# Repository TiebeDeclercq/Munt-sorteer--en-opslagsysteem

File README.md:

<!-- PROJECT LOGO -->
<br />
<div align="center">

  <h3 align="center">Coin sorting and storage system</h3>

  <p align="center">
    A coin-counting, storing, and dispensing system.
    <br />
    <a href="https://giptiebedeclercq.wordpress.com/"><strong>View the blog »</strong></a>
    <br />
    <br />
  </p>
</div>

<!-- ABOUT THE PROJECT -->
## About The Project

My design is a coin sorting and storage system aimed at effectively addressing the issue of loose change in the household. By storing all your coins in one central location, all the inconveniences of scattered small change are eliminated, and you have an accurate overview of your available loose change at all times. In this document, I will meticulously walk through the various phases of the project, detailing the development and implementation of the coin sorting and storage system step by step. All necessary information, including components and diagrams, is included in my document, accompanied by comprehensive explanations for a clear overview of the entire process.

## Download the software
This is the general software to control the coinsorting system for simply storing you're coins
<p float="left">
  <a href="https://play.google.com/store/apps/details?id=com.Ti3b3.Coin_sorting_and_storage_system"></img></a>
  <a href="https://l.messenger.com/l.php?u=http%3A%2F%2Fitunes.apple.com%2Fapp%2Fid6480136312&h=AT0W5dLV4-_HWo6Hpzhd1CNAs4ooRaiCPJcBq9KRZzaV246Ko3VcdnYeWSVa93cHaYDz-uc7uD9_STlt7n5DoX44x320C2RBlRl9Fa9wpZAEIEF3_ePi8t-rp98hANBxP2WmDY1l13mO-Vc"></img></a>
  <a href="https://apps.microsoft.com/detail/9ndc85wl55n7?hl=nl-nl&gl=BE"></img></a>
</p>

This is sofware/game to play flappy bird but you can play with multiple people and compete against eatchother 

<a href="https://ti3b3.itch.io/coin-sorting-and-storage-system-flappy-bird"></img></a>

<p align="right">(<a href="#readme-top">back to top</a>)</p>

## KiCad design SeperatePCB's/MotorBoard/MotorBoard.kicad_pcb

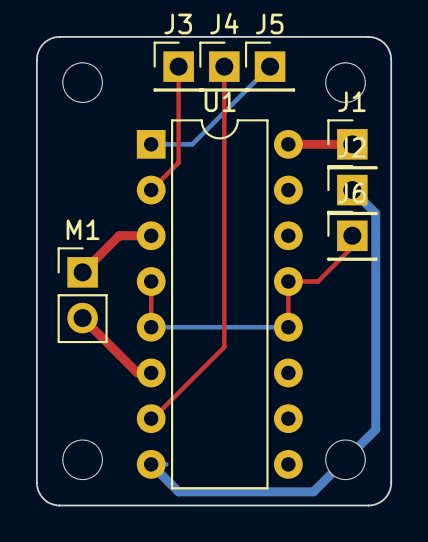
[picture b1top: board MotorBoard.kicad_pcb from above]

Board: 2 copper layers, 19.7 x 26.0 mm, 12 parts (0 on the bottom side), 8 nets.

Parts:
H1, H2, H3, H4: MountingHole; MountingHole_2.2mm_M2
J1, J2, J3, J4, J5, J6: Conn_01x01_Pin; PinHeader_1x01_P2.54mm_Vertical
M1: Motor_DC; PinHeader_1x02_P2.54mm_Vertical
U1: L293D; DIP-16_W7.62mm

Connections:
unnamed: J1.1, U1.16 (VCC1)
unnamed: J2.1, U1.8 (VCC2)
unnamed: J3.1, U1.2 (1A)
unnamed: J4.1, U1.7 (2A)
unnamed: J5.1, U1.1 (EN1,2)
unnamed: J6.1, U1.4 (GND), U1.5 (GND), U1.12 (GND), U1.13 (GND)
unnamed: M1.1 (+), U1.3 (1Y)
unnamed: M1.2 (-), U1.6 (2Y)

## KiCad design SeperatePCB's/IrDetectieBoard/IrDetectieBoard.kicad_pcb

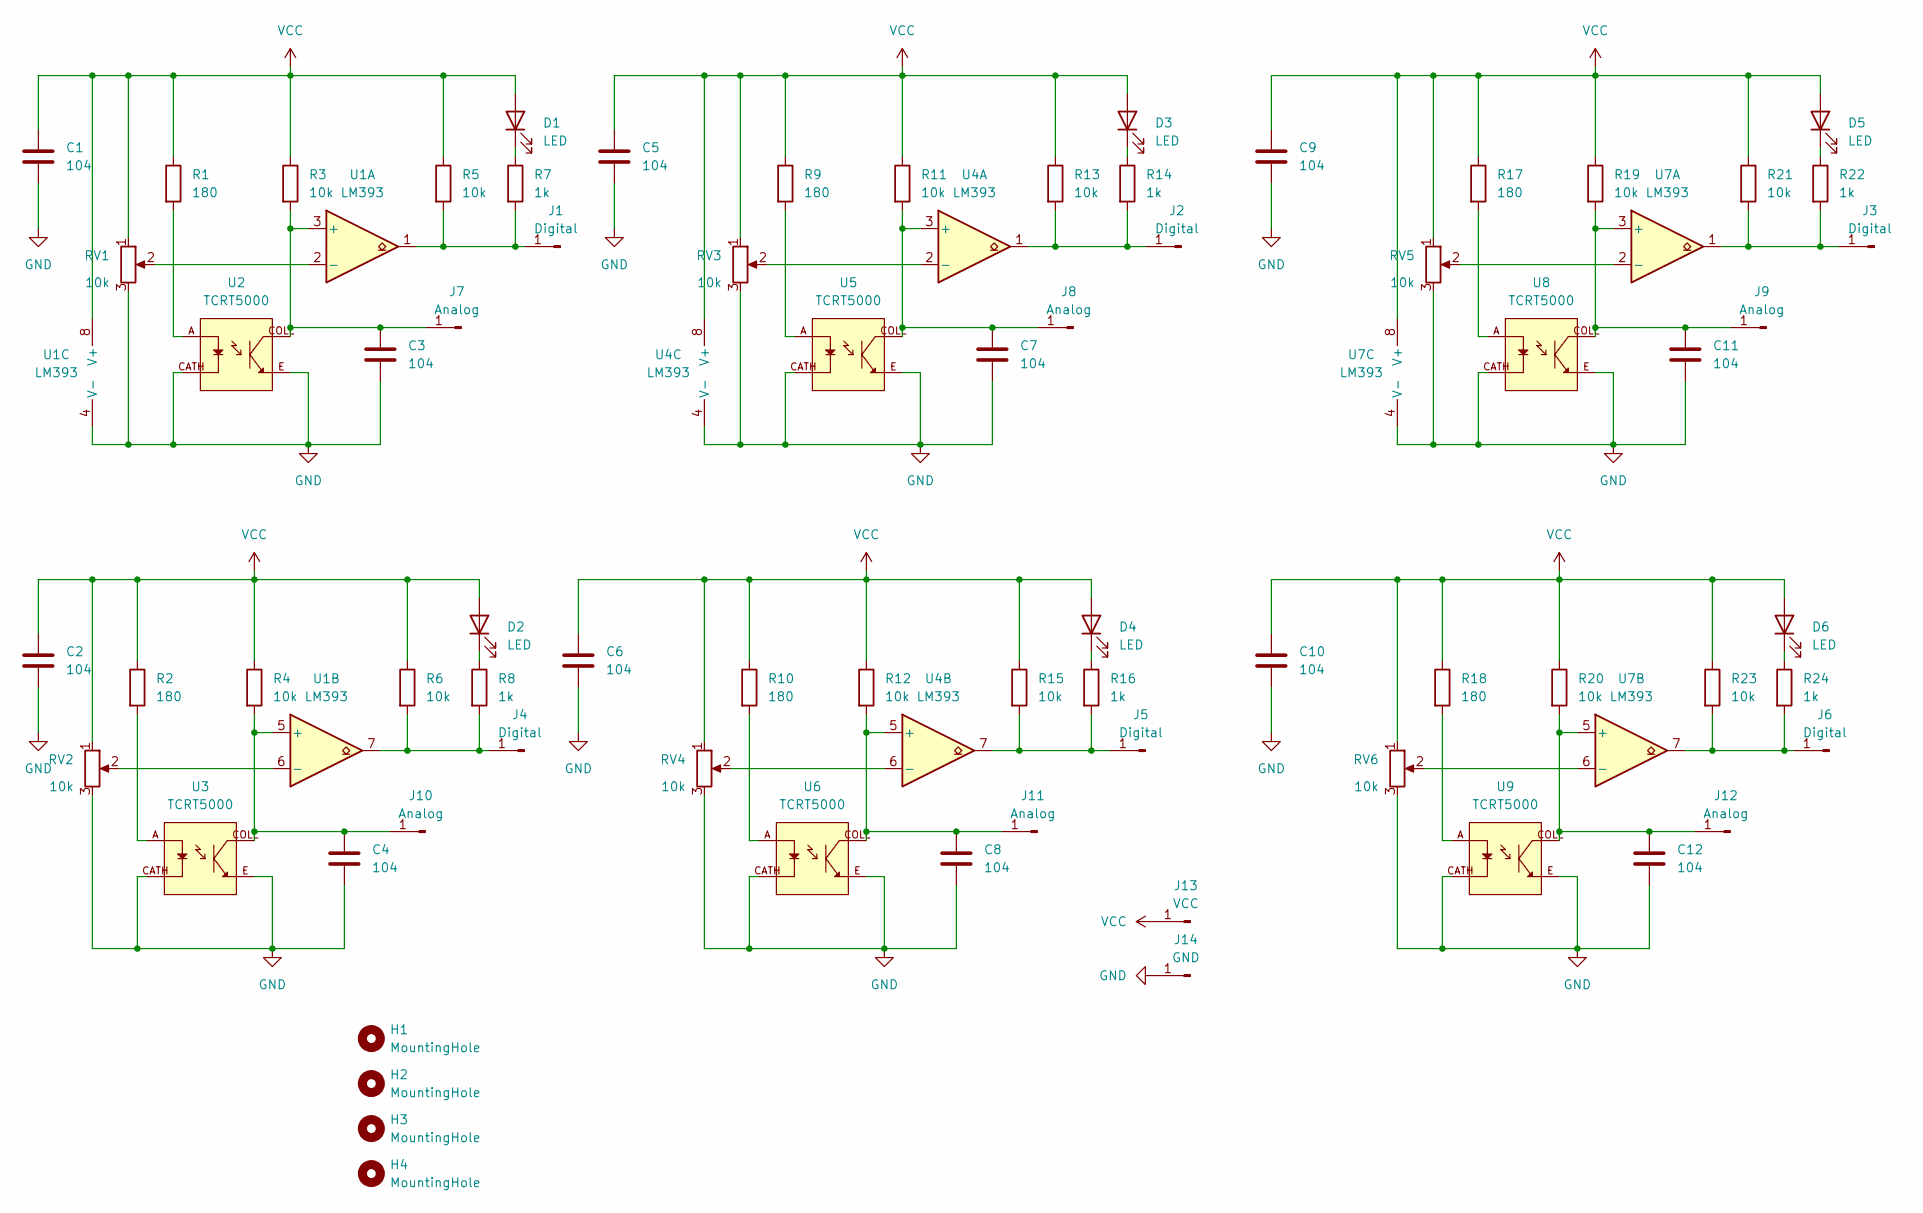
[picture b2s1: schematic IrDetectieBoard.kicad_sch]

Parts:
C1, C2, C3, C4, C5, C6, C7, C8, C9, C10, C11, C12: 104; C_0805_2012Metric_Pad1.18x1.45mm_HandSolder
D1, D2, D3, D4, D5, D6: LED; LED_0805_2012Metric_Pad1.15x1.40mm_HandSolder
H1, H2, H3, H4: MountingHole; MountingHole_2.2mm_M2
J1, J2, J3, J4, J5, J6: Digital; PinHeader_1x01_P2.54mm_Vertical
J7, J8, J9, J10, J11, J12: Analog; PinHeader_1x01_P2.54mm_Vertical
J13: VCC; PinHeader_1x01_P2.54mm_Vertical
J14: GND; PinHeader_1x01_P2.54mm_Vertical
R1, R2, R9, R10, R17, R18: 180; R_0805_2012Metric_Pad1.20x1.40mm_HandSolder
R3, R4, R5, R6, R11, R12, R13, R15, R19, R20, R21, R23: 10k; R_0805_2012Metric_Pad1.20x1.40mm_HandSolder
R7, R8, R14, R16, R22, R24: 1k; R_0805_2012Metric_Pad1.20x1.40mm_HandSolder
RV1, RV2, RV3, RV4, RV5, RV6: 10k; Potentiometer_Bourns_3296W_Vertical
U1, U4, U7: LM393; SO-8_3.9x4.9mm_P1.27mm
U2, U3, U5, U6, U8, U9: TCRT5000; PARTREV 1.7

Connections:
GND: C1.2, C2.2, C3.2, C4.2, C5.2, C6.2, C7.2, C8.2, C9.2, C10.2, C11.2, C12.2, J14.1, RV1.3, RV2.3, RV3.3, RV4.3, RV5.3, RV6.3, U1.4 (V-), U2.CATH, U2.E, U3.CATH, U3.E, U4.4 (V-), U5.CATH, U5.E, U6.CATH, U6.E, U7.4 (V-), U8.CATH, U8.E, U9.CATH, U9.E
unnamed: D1.1 (K), R7.1
unnamed: D2.1 (K), R8.1
unnamed: D3.1 (K), R14.1
unnamed: D4.1 (K), R16.1
unnamed: D5.1 (K), R22.1
unnamed: D6.1 (K), R24.1
unnamed: J1.1, R5.2, R7.2, U1.1
unnamed: J2.1, R13.2, R14.2, U4.1
unnamed: J3.1, R21.2, R22.2, U7.1
unnamed: J4.1, R6.2, R8.2, U1.7
unnamed: J5.1, R15.2, R16.2, U4.7
unnamed: J6.1, R23.2, R24.2, U7.7
unnamed: C3.1, J7.1, R3.2, U1.3 (+), U2.COLL
unnamed: C7.1, J8.1, R11.2, U4.3 (+), U5.COLL
unnamed: C11.1, J9.1, R19.2, U7.3 (+), U8.COLL
unnamed: C4.1, J10.1, R4.2, U1.5 (+), U3.COLL
unnamed: C8.1, J11.1, R12.2, U4.5 (+), U6.COLL
unnamed: C12.1, J12.1, R20.2, U7.5 (+), U9.COLL
unnamed: R1.2, U2.A
unnamed: R2.2, U3.A
unnamed: R9.2, U5.A
unnamed: R10.2, U6.A
unnamed: R17.2, U8.A
unnamed: R18.2, U9.A
unnamed: RV1.2, U1.2 (-)
unnamed: RV2.2, U1.6 (-)
unnamed: RV3.2, U4.2 (-)
unnamed: RV4.2, U4.6 (-)
unnamed: RV5.2, U7.2 (-)
unnamed: RV6.2, U7.6 (-)
VCC: C1.1, C2.1, C5.1, C6.1, C9.1, C10.1, D1.2 (A), D2.2 (A), D3.2 (A), D4.2 (A), D5.2 (A), D6.2 (A), J13.1, R1.1, R2.1, R3.1, R4.1, R5.1, R6.1, R9.1, R10.1, R11.1, R12.1, R13.1, R15.1, R17.1, R18.1, R19.1, R20.1, R21.1, R23.1, RV1.1, RV2.1, RV3.1, RV4.1, RV5.1, RV6.1, U1.8 (V+), U4.8 (V+), U7.8 (V+)

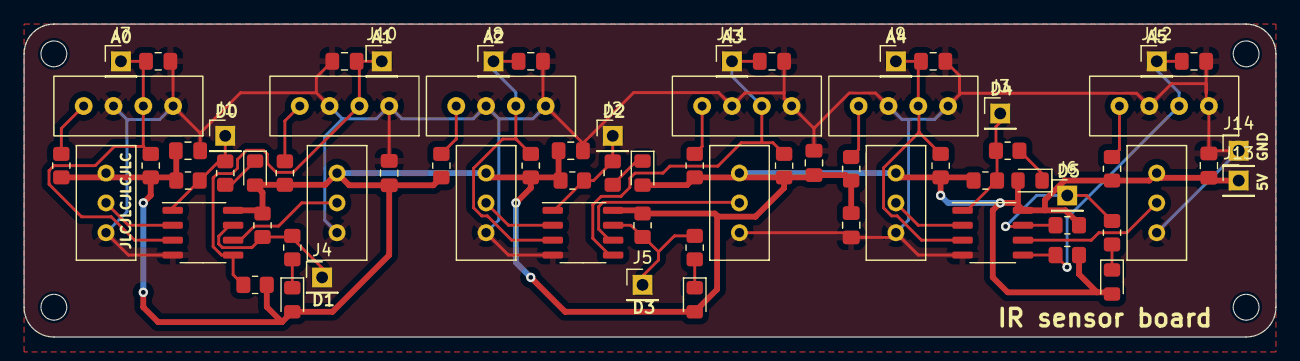
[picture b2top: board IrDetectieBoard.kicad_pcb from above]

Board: 2 copper layers, 106.7 x 26.7 mm, 75 parts (0 on the bottom side), 32 nets.

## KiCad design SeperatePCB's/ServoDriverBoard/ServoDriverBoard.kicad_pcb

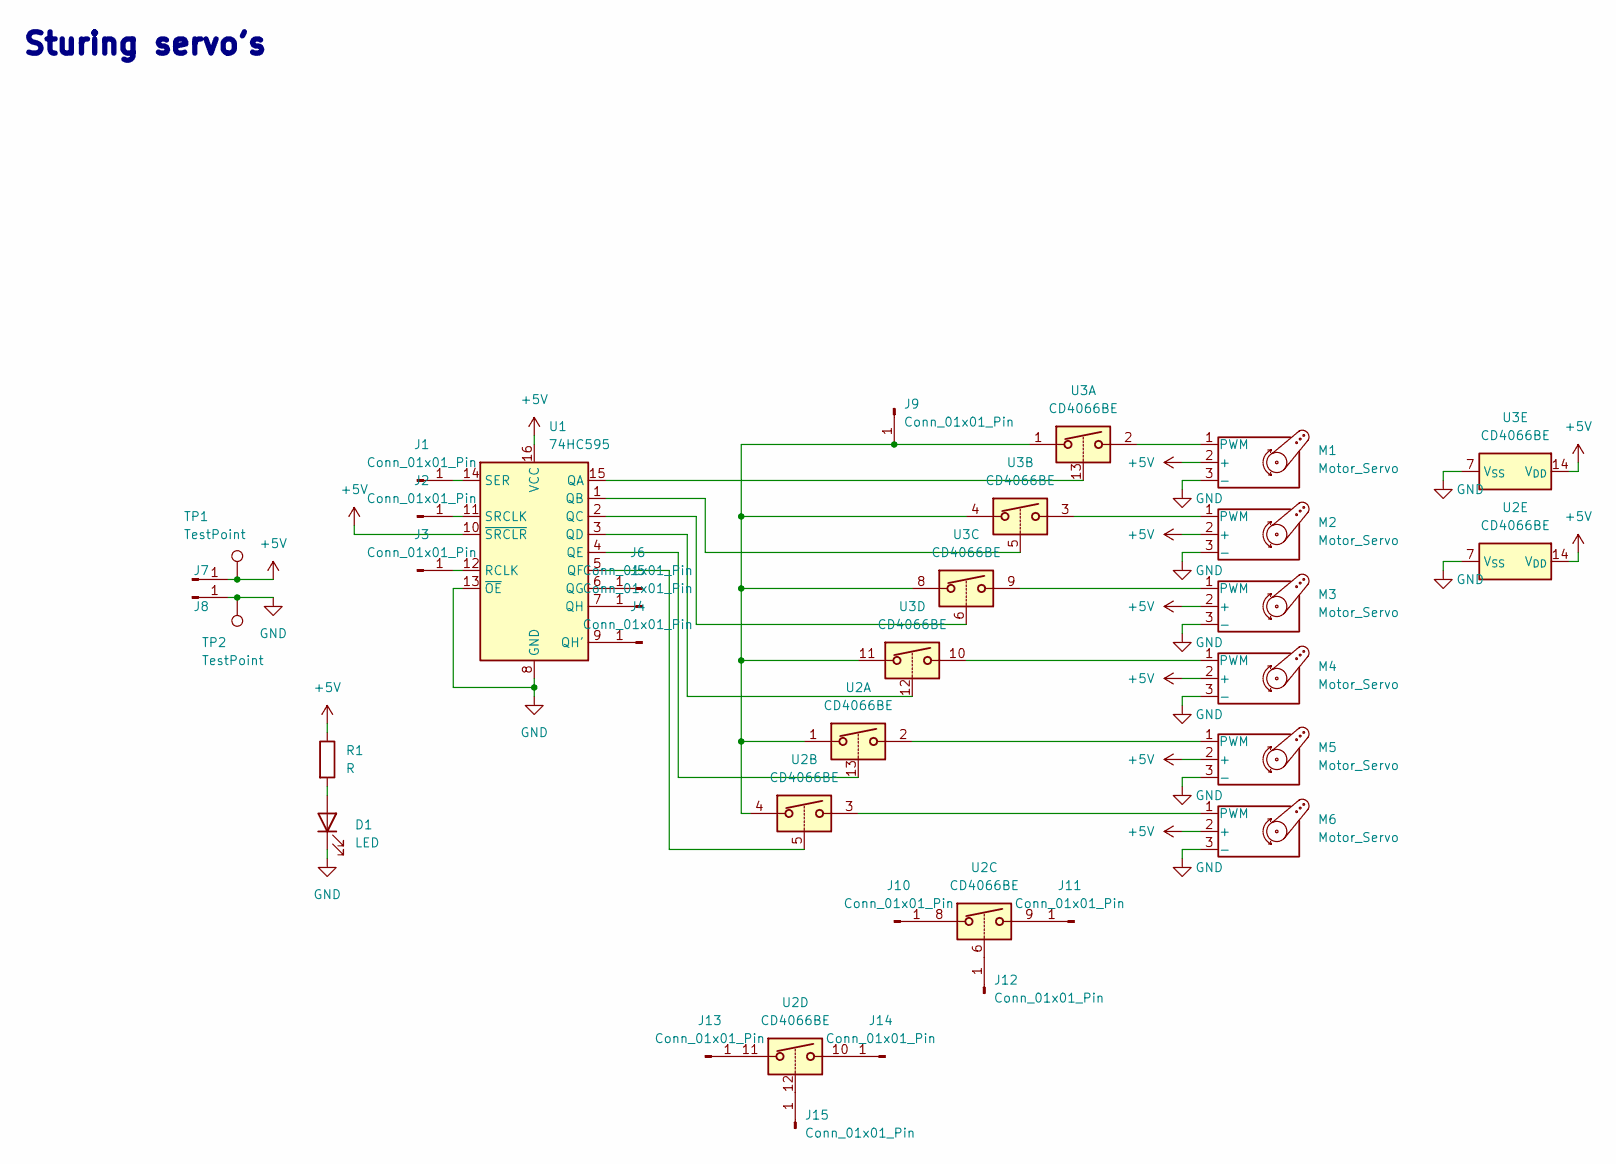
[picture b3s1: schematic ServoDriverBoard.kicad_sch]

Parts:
D1: LED; LED_0805_2012Metric_Pad1.15x1.40mm_HandSolder
J1, J2, J3, J4, J5, J6, J7, J8, J9, J10, J11, J12, J13, J14, J15: Conn_01x01_Pin; PinHeader_1x01_P2.54mm_Vertical
M1, M2, M3, M4, M5, M6: Motor_Servo; PinHeader_1x03_P2.54mm_Vertical
R1: R; R_0805_2012Metric_Pad1.20x1.40mm_HandSolder
TP1, TP2: TestPoint; TestPoint_Pad_D1.5mm
U1: 74HC595; DIP-16_W7.62mm_Socket
U2, U3: CD4066BE; DIP-14_W7.62mm_Socket

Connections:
+5V: J7.1, M1.2 (+), M2.2 (+), M3.2 (+), M4.2 (+), M5.2 (+), M6.2 (+), R1.1, TP1.1, U1.10 (~SRCLR), U1.16 (VCC), U2.14 (V_{DD}), U3.14 (V_{DD})
GND: D1.1 (K), J8.1, M1.3 (-), M2.3 (-), M3.3 (-), M4.3 (-), M5.3 (-), M6.3 (-), TP2.1, U1.8 (GND), U1.13 (~OE), U2.7 (V_{SS}), U3.7 (V_{SS})
unnamed: D1.2 (A), R1.2
unnamed: J1.1, U1.14 (SER)
unnamed: J2.1, U1.11 (SRCLK)
unnamed: J3.1, U1.12 (RCLK)
unnamed: J4.1, U1.9 (QH')
unnamed: J5.1, U1.7 (QH)
unnamed: J6.1, U1.6 (QG)
unnamed: J9.1, U2.1, U2.4, U3.1, U3.4, U3.8, U3.11
unnamed: J10.1, U2.8
unnamed: J11.1, U2.9
unnamed: J12.1, U2.6
unnamed: J13.1, U2.11
unnamed: J14.1, U2.10
unnamed: J15.1, U2.12
unnamed: M1.1 (PWM), U3.2
unnamed: M2.1 (PWM), U3.3
unnamed: M3.1 (PWM), U3.9
unnamed: M4.1 (PWM), U3.10
unnamed: M5.1 (PWM), U2.2
unnamed: M6.1 (PWM), U2.3
unnamed: U1.15 (QA), U3.13
unnamed: U1.1 (QB), U3.5
unnamed: U1.2 (QC), U3.6
unnamed: U1.3 (QD), U3.12
unnamed: U1.4 (QE), U2.13
unnamed: U1.5 (QF), U2.5

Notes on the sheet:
Sturing servo's

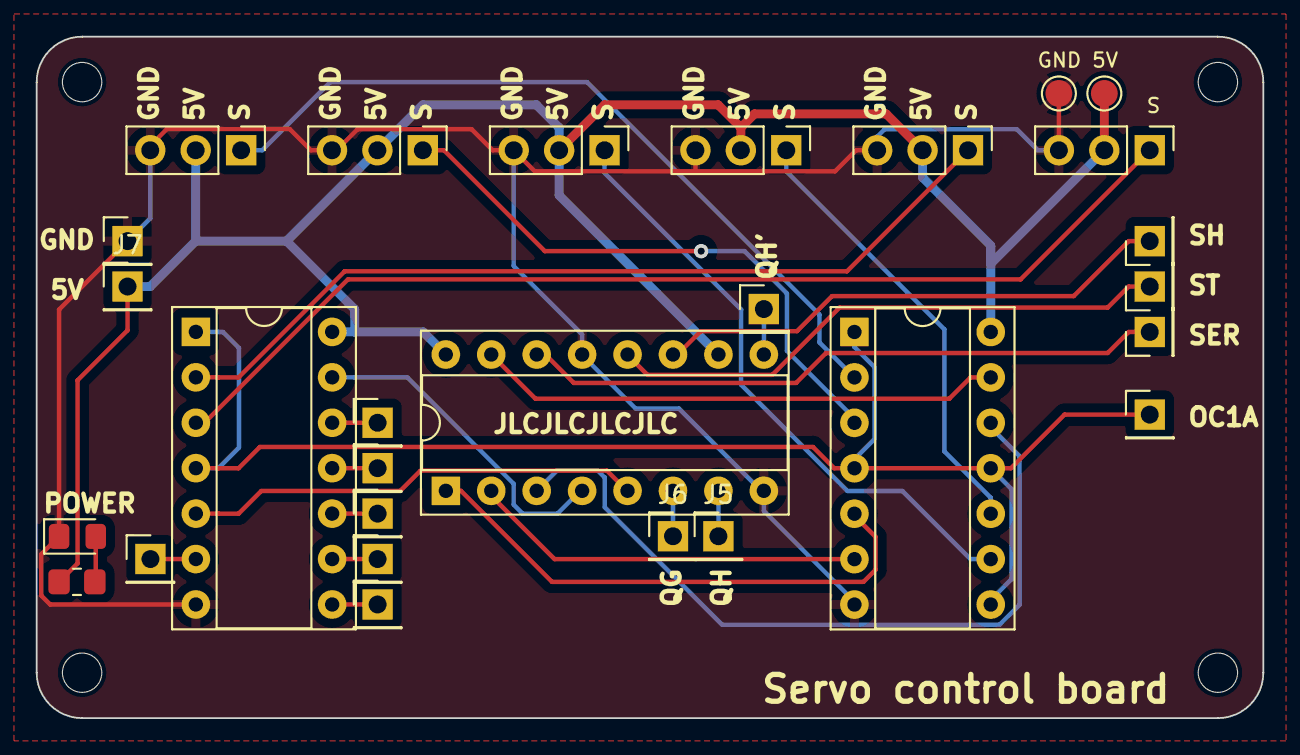
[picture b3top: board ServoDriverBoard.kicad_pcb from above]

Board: 2 copper layers, 68.6 x 38.1 mm, 32 parts (0 on the bottom side), 28 nets.

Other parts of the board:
H1, H2, H3, H4: MountingHole; MountingHole_2.2mm_M2

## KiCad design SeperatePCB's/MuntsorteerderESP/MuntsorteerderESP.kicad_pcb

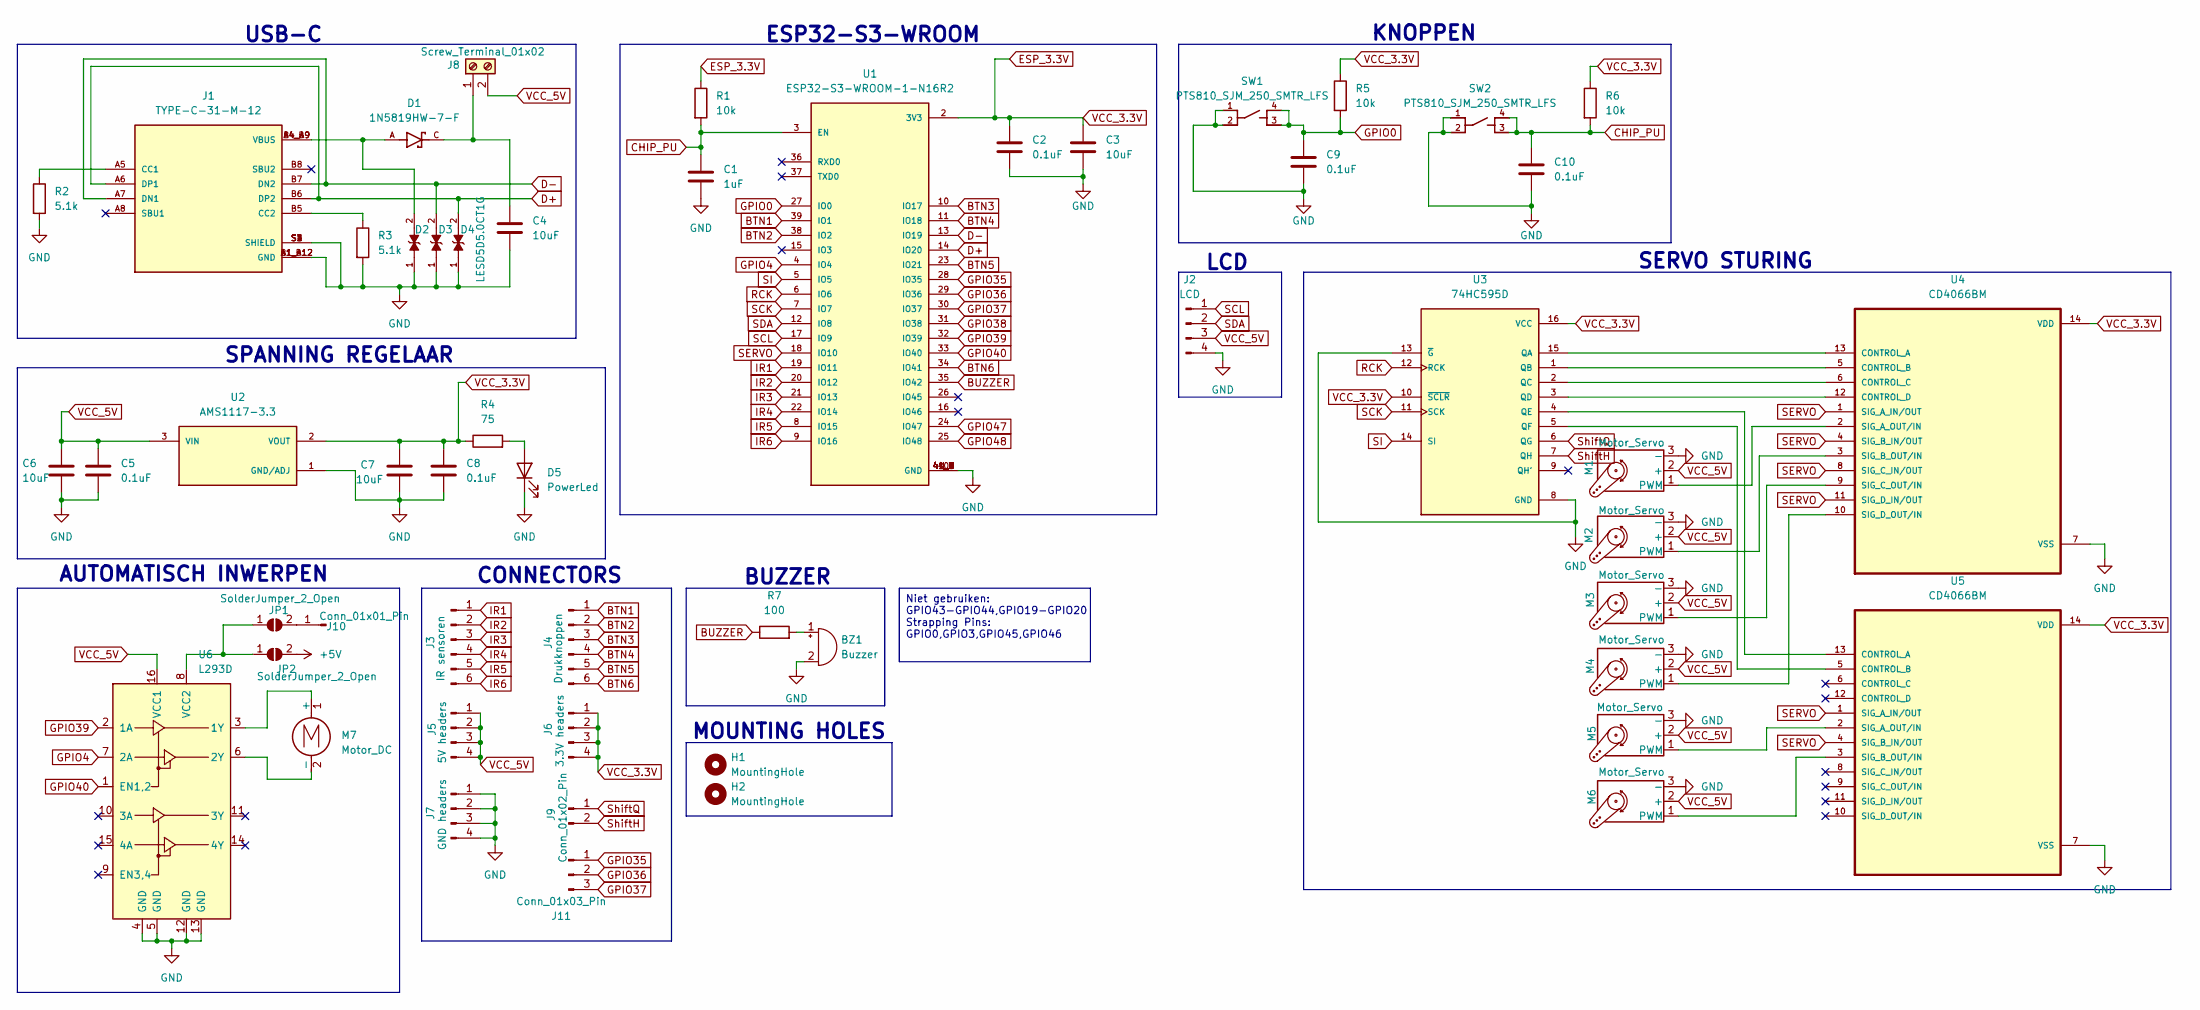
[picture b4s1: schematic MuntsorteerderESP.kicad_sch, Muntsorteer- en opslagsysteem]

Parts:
BZ1: Buzzer; Buzzer_12x9.5RM7.6
C1: 1uF; C_0805_2012Metric_Pad1.18x1.45mm_HandSolder
C2, C5, C8, C9, C10: 0.1uF; C_0805_2012Metric_Pad1.18x1.45mm_HandSolder
C3, C4, C6, C7: 10uF; C_0805_2012Metric_Pad1.18x1.45mm_HandSolder
D1: 1N5819HW-7-F; SOD3715X145N; PARTREV 18-2
D2, D3, D4: LESD5D5.0CT1G; TVS_LESD5D5.0CT1G; PARTREV O
D5: PowerLed; LED_0805_2012Metric
H1, H2: MountingHole; MountingHole_3.2mm_M3
J1: TYPE-C-31-M-12; HRO_TYPE-C-31-M-12; PARTREV 2020.12.08
J2: LCD; PinHeader_1x04_P2.54mm_Vertical
J3: IR sensoren; PinHeader_1x06_P2.54mm_Vertical
J4: Drukknoppen; PinHeader_1x06_P2.54mm_Vertical
J5: 5V headers; PinHeader_1x04_P2.54mm_Vertical
J6: 3.3V headers; PinHeader_1x04_P2.54mm_Vertical
J7: GND headers; PinHeader_1x04_P2.54mm_Vertical
J8: Screw_Terminal_01x02; TerminalBlock_Phoenix_MKDS-1,5-2-5.08_1x02_P5.08mm_Horizont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
J9: Conn_01x02_Pin; PinHeader_1x02_P2.54mm_Vertical
J10: Conn_01x01_Pin; PinHeader_1x01_P2.54mm_Vertical
J11: Conn_01x03_Pin; PinHeader_1x03_P2.54mm_Vertical
JP1, JP2: SolderJumper_2_Open; SolderJumper-2_P1.3mm_Open_RoundedPad1.0x1.5mm
M1, M2, M3, M4, M5, M6: Motor_Servo; PinHeader_1x03_P2.54mm_Vertical
M7: Motor_DC; TerminalBlock_Phoenix_MKDS-1,5-2-5.08_1x02_P5.08mm_Horizont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
R1, R5, R6: 10k; R_0805_2012Metric_Pad1.20x1.40mm_HandSolder
R2, R3: 5.1k; R_0805_2012Metric_Pad1.20x1.40mm_HandSolder
R4: 75; R_0805_2012Metric_Pad1.20x1.40mm_HandSolder
R7: 100; R_0805_2012Metric_Pad1.20x1.40mm_HandSolder
SW1, SW2: PTS810_SJM_250_SMTR_LFS; SW_PTS810_SJM_250_SMTR_LFS
U1: ESP32-S3-WROOM-1-N16R2; XCVR_ESP32-S3-WROOM-1-N16R2; PARTREV v1.0
U2: AMS1117-3.3; SOT229P700X180-4N; PARTREV N/A
U3: 74HC595D; SOP127P600X175-16N; PARTREV 4.0
U4, U5: CD4066BM; SOIC127P600X175-14N
U6: L293D; DIP-16_W7.62mm

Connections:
+5V: JP2.2 (B)
BTN1: J4.1, U1.39 (IO1)
BTN2: J4.2, U1.38 (IO2)
BTN3: J4.3, U1.10 (IO17)
BTN4: J4.4, U1.11 (IO18)
BTN5: J4.5, U1.23 (IO21)
BTN6: J4.6, U1.34 (IO41)
BUZZER: R7.1, U1.35 (IO42)
CHIP_PU: C1.1, C10.1, R1.2, R6.2, SW2.3, SW2.4, U1.3 (EN)
D+: D4.2, J1.A6 (DP1), J1.B6 (DP2), U1.14 (IO20)
D-: D3.2, J1.A7 (DN1), J1.B7 (DN2), U1.13 (IO19)
ESP_3.3V: C2.1, C3.1, C7.1, C8.1, J6.1, J6.2, J6.3, J6.4, R1.1, R4.1, R5.1, R6.1, U1.2 (3V3), U2.2 (VOUT), U3.10 (~SCLR), U3.16 (VCC), U4.14 (VDD), U5.14 (VDD)
GND: BZ1.2 (+), C1.2, C2.2, C3.2, C4.2, C5.2, C6.2, C7.2, C8.2, C9.2, C10.2, D2.1, D3.1, D4.1, D5.1 (K), J1.A1_B12 (GND), J1.B1_A12 (GND), J1.S1 (SHIELD), J1.S2 (SHIELD), J1.S3 (SHIELD), J1.S4 (SHIELD), J2.4, J7.1, J7.2, J7.3, J7.4, M1.3 (-), M2.3 (-), M3.3 (-), M4.3 (-), M5.3 (-), M6.3 (-), R2.2, R3.2, SW1.1, SW1.2, SW2.1, SW2.2, U1.1 (GND), U1.40 (GND), U1.41_1 (GND), U1.41_2 (GND), U1.41_3 (GND), U1.41_4 (GND), U1.41_5 (GND), U1.41_6 (GND), U1.41_7 (GND), U1.41_8 (GND), U1.41_9 (GND), U2.1 (GND/ADJ), U3.8 (GND), U3.13 (~G), U4.7 (VSS), U5.7 (VSS), U6.4 (GND), U6.5 (GND), U6.12 (GND), U6.13 (GND)
GPIO0: C9.1, R5.2, SW1.3, SW1.4, U1.27 (IO0)
GPIO4: U1.4 (IO4), U6.7 (2A)
GPIO35: J11.1, U1.28 (IO35)
GPIO36: J11.2, U1.29 (IO36)
GPIO37: J11.3, U1.30 (IO37)
GPIO38: U1.31 (IO38)
GPIO39: U1.32 (IO39), U6.2 (1A)
GPIO40: U1.33 (IO40), U6.1 (EN1,2)
GPIO47: U1.24 (IO47)
GPIO48: U1.25 (IO48)
IR1: J3.1, U1.19 (IO11)
IR2: J3.2, U1.20 (IO12)
IR3: J3.3, U1.21 (IO13)
IR4: J3.4, U1.22 (IO14)
IR5: J3.5, U1.8 (IO15)
IR6: J3.6, U1.9 (IO16)
unnamed: BZ1.1 (-), R7.2
unnamed: D1.A, D2.2, J1.A4_B9 (VBUS), J1.B4_A9 (VBUS)
unnamed: D5.2 (A), R4.2
unnamed: J1.A5 (CC1), R2.1
unnamed: J1.B5 (CC2), R3.1
unnamed: C4.1, D1.C, J8.1
unnamed: J10.1, JP1.2 (B)
unnamed: JP1.1 (A), JP2.1 (A), U6.8 (VCC2)
unnamed: M1.1 (PWM), U4.2 (SIG_A_OUT/IN)
unnamed: M2.1 (PWM), U4.3 (SIG_B_OUT/IN)
unnamed: M3.1 (PWM), U4.9 (SIG_C_OUT/IN)
unnamed: M4.1 (PWM), U4.10 (SIG_D_OUT/IN)
unnamed: M5.1 (PWM), U5.2 (SIG_A_OUT/IN)
unnamed: M6.1 (PWM), U5.3 (SIG_B_OUT/IN)
unnamed: M7.1 (+), U6.3 (1Y)
unnamed: M7.2 (-), U6.6 (2Y)
unnamed: U3.15 (QA), U4.13 (CONTROL_A)
unnamed: U3.1 (QB), U4.5 (CONTROL_B)
unnamed: U3.2 (QC), U4.6 (CONTROL_C)
unnamed: U3.3 (QD), U4.12 (CONTROL_D)
unnamed: U3.4 (QE), U5.13 (CONTROL_A)
unnamed: U3.5 (QF), U5.5 (CONTROL_B)
RCK: U1.6 (IO6), U3.12 (RCK)
SCK: U1.7 (IO7), U3.11 (SCK)
SCL: J2.1, U1.17 (IO9)
SDA: J2.2, U1.12 (IO8)
SERVO: U1.18 (IO10), U4.1 (SIG_A_IN/OUT), U4.4 (SIG_B_IN/OUT), U4.8 (SIG_C_IN/OUT), U4.11 (SIG_D_IN/OUT), U5.1 (SIG_A_IN/OUT), U5.4 (SIG_B_IN/OUT)
SI: U1.5 (IO5), U3.14 (SI)
ShiftH: J9.2, U3.7 (QH)
ShiftQ: J9.1, U3.6 (QG)
VCC_5V: C5.1, C6.1, J2.3, J5.1, J5.2, J5.3, J5.4, J8.2, M1.2 (+), M2.2 (+), M3.2 (+), M4.2 (+), M5.2 (+), M6.2 (+), U2.3 (VIN), U6.16 (VCC1)

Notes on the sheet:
Niet gebruiken: GPIO43-GPIO44,GPIO19-GPIO20 Strapping Pins: GPIO0,GPIO3,GPIO45,GPIO46
AUTOMATISCH INWERPEN
BUZZER
MOUNTING HOLES
USB-C
SERVO STURING
LCD
CONNECTORS
SPANNING REGELAAR
KNOPPEN
ESP32-S3-WROOM

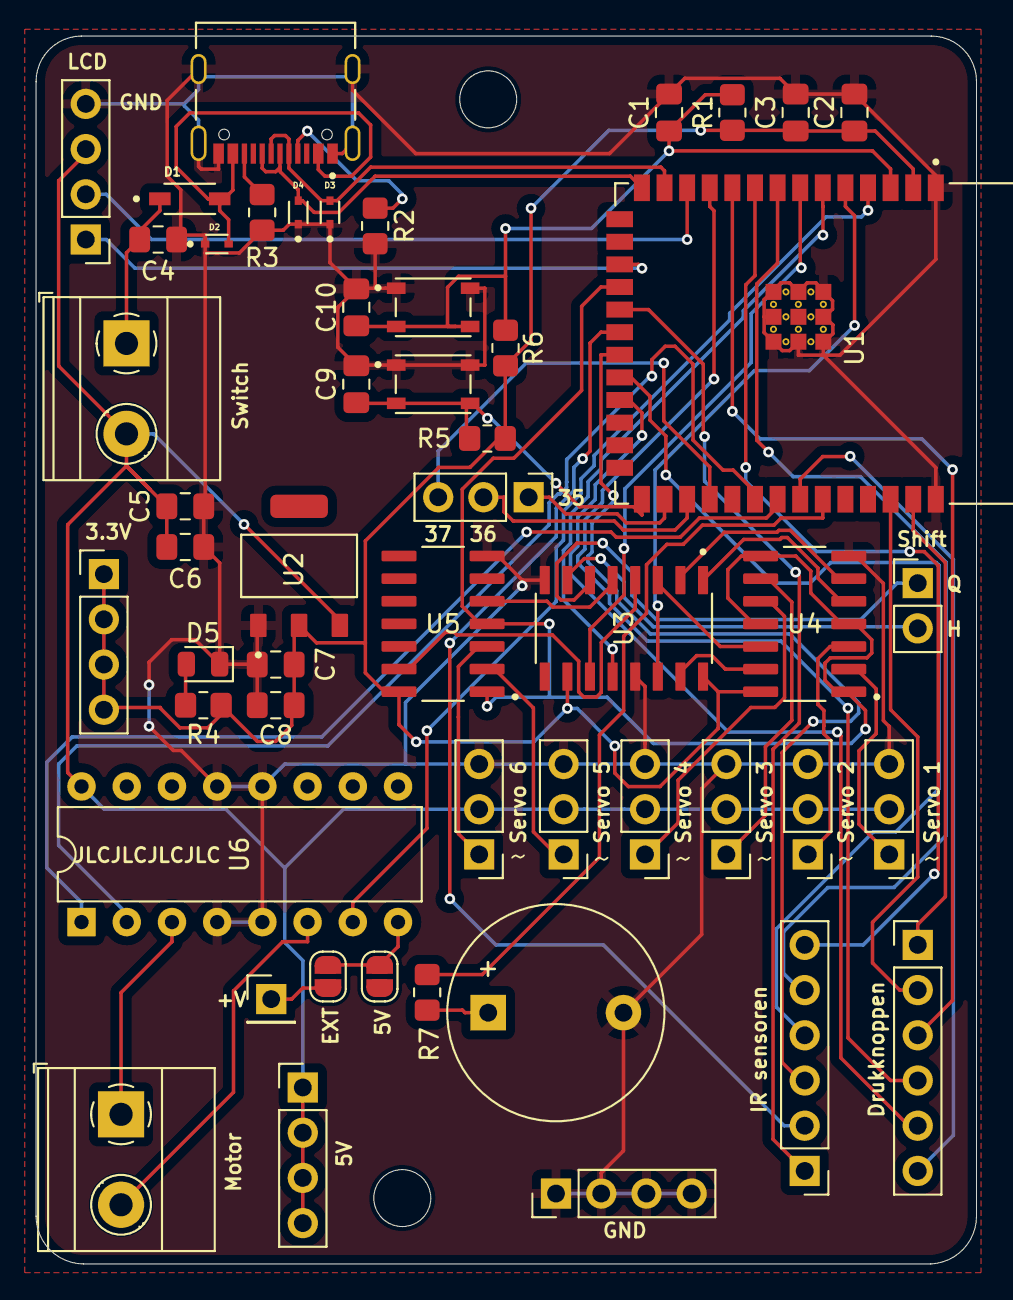
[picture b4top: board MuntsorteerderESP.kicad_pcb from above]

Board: 2 copper layers, 52.8 x 69.0 mm, 53 parts (0 on the bottom side), 56 nets.

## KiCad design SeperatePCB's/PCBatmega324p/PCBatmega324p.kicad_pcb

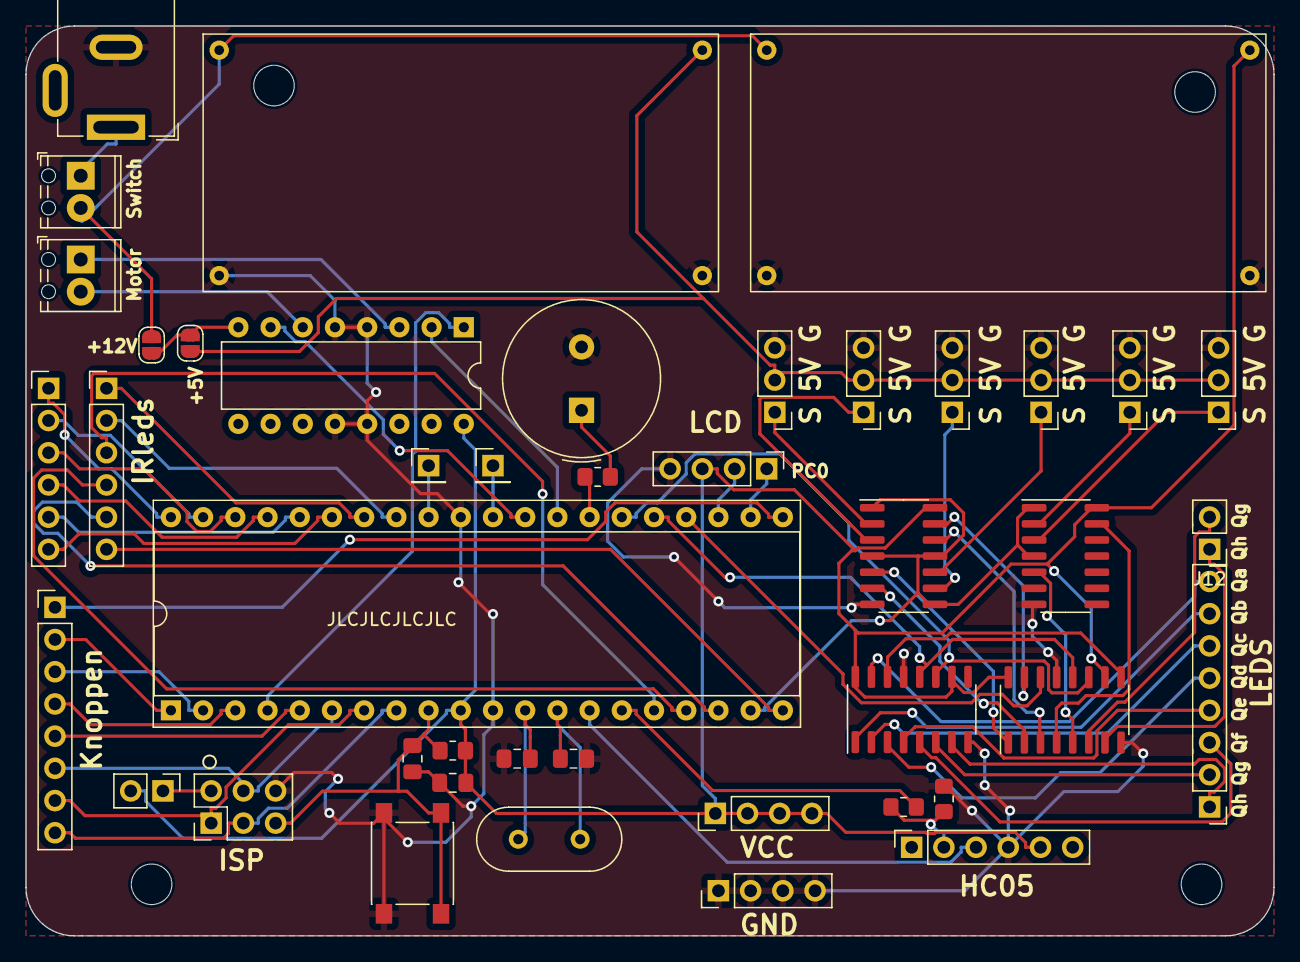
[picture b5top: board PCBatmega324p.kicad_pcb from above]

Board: 2 copper layers, 98.4 x 71.8 mm, 47 parts (0 on the bottom side), 71 nets.

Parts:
BZ1: Buzzer; Buzzer_TDK_PS1240P02BT_D12.2mm_H6.5mm
C13, C18: 100nF; C_0805_2012Metric_Pad1.18x1.45mm_HandSolder
C16, C17: 22pF; C_0805_2012Metric_Pad1.18x1.45mm_HandSolder
H1, H2, H3, H4: MountingHole; MountingHole_3.2mm_M3
J1: Barrel_Jack; BarrelJack_GCT_DCJ200-10-A_Horizontal
J2: Conn_01x06_Socket; PinSocket_1x06_P2.54mm_Vertical
J3: AVR-ISP-6; PinHeader_2x03_P2.54mm_Vertical
J5: LCDconn; PinHeader_1x04_P2.54mm_Vertical
J6: Screw_Terminal_01x02; TerminalBlock_Phoenix_MPT-0,5-2-2.54_1x02_P2.54mm_Horizontal
J7, J8: portD_21; PinHeader_1x01_P2.54mm_Vertical
J9, J10: Conn_01x04_Pin; PinHeader_1x04_P2.54mm_Vertical
J11, J14: Conn_01x06_Pin; PinHeader_1x06_P2.54mm_Vertical
J12: Conn_01x02_Pin; PinHeader_1x02_P2.54mm_Vertical
J13, J15: Conn_01x08_Pin; PinHeader_1x08_P2.54mm_Vertical
JP1, JP2: SolderJumper_2_Open; SolderJumper-2_P1.3mm_Open_RoundedPad1.0x1.5mm
JP7: Jumper_2_Open; PinHeader_1x02_P2.54mm_Vertical
M1: Motor_DC; TerminalBlock_Phoenix_MPT-0,5-2-2.54_1x02_P2.54mm_Horizontal
M2, M3, M4, M5, M6, M7: Motor_Servo; PinHeader_1x03_P2.54mm_Vertical
R1, R2, R45: 10KΩ; R_0805_2012Metric_Pad1.20x1.40mm_HandSolder
R33: 100; R_0805_2012Metric_Pad1.20x1.40mm_HandSolder
SW9: SW_Push; SW_SPST_PTS645
U1: L293D; DIP-16_W7.62mm
U10, U11: Buck_Converter
U15: ATmega324P-20P; DIP-40_W15.24mm_Socket
U20, U21: 74HC595; SO-16_3.9x9.9mm_P1.27mm
U22, U23: CD4066BE; SO-14_3.9x8.65mm_P1.27mm
Y1: Crystal; Crystal_HC49-4H_Vertical

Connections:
+5V: JP2.2 (B), M2.2 (+), M3.2 (+), M4.2 (+), M5.2 (+), M6.2 (+), M7.2 (+), U10.OUT+
+12V: J6.2, JP1.2 (B), U10.IN+, U11.IN+
/AREF: J7.1, U15.32 (AREF)
/AVCC: J8.1, U15.30 (AVCC)
GND: BZ1.2 (+), C13.2, C16.2, C17.2, C18.1, J1.2, J2.4, J3.6 (GND), J5.4, J10.1, J10.2, J10.3, J10.4, M2.3 (-), M3.3 (-), M4.3 (-), M5.3 (-), M6.3 (-), M7.3 (-), R2.2, SW9.1, U1.4 (GND), U1.5 (GND), U1.12 (GND), U1.13 (GND), U10.IN-, U10.OUT-, U11.IN-, U11.OUT-, U15.11 (GND), U15.31 (GND), U20.8 (GND), U20.13 (~OE), U21.8 (GND), U21.13 (~OE), U22.7 (V_{SS}), U23.7 (V_{SS})
unnamed: BZ1.1 (-), R33.2
unnamed: J2.2, R1.2, R2.1
unnamed: J3.2 (VCC), JP7.1 (A)
unnamed: J1.1, J6.1
unnamed: J12.1, U20.7 (QH)
unnamed: J12.2, U20.6 (QG)
unnamed: J13.1, U21.7 (QH)
unnamed: J13.2, U21.6 (QG)
unnamed: J13.3, U21.5 (QF)
unnamed: J13.4, U21.4 (QE)
unnamed: J13.5, U21.3 (QD)
unnamed: J13.6, U21.2 (QC)
unnamed: J13.7, U21.1 (QB)
unnamed: J13.8, U21.15 (QA)
unnamed: JP1.1 (A), JP2.1 (A), U1.8 (VCC2)
unnamed: M1.1 (+), U1.3 (1Y)
unnamed: M1.2 (-), U1.6 (2Y)
unnamed: M2.1 (PWM), U23.2
unnamed: M3.1 (PWM), U23.3
unnamed: M4.1 (PWM), U23.9
unnamed: M5.1 (PWM), U23.10
unnamed: M6.1 (PWM), U22.2
unnamed: M7.1 (PWM), U22.3
unnamed: C16.1, U15.13 (XTAL1), Y1.2
unnamed: C17.1, U15.12 (XTAL2), Y1.1
unnamed: U20.15 (QA), U23.13
unnamed: U20.1 (QB), U23.5
unnamed: U20.2 (QC), U23.6
unnamed: U20.3 (QD), U23.12
unnamed: U20.4 (QE), U22.13
unnamed: U20.5 (QF), U22.5
unnamed: U20.9 (QH'), U21.14 (SER)
PA0: J11.1, U15.40 (PA0)
PA1: J11.2, U15.39 (PA1)
PA2: J11.3, U15.38 (PA2)
PA3: J11.4, U15.37 (PA3)
PA4: J11.5, U15.36 (PA4)
PA5: J11.6, U15.35 (PA5)
PA6: J14.1, U15.34 (PA6)
PA7: J14.2, U15.33 (PA7)
PB0: J15.2, U15.1 (PB0)
PB1: J15.3, U15.2 (PB1)
PB2: J15.4, U15.3 (PB2)
PB3: U1.1 (EN1,2), U15.4 (PB3)
PB4: J15.5, U15.5 (PB4)
PB5: J3.4 (MOSI), J15.6, U15.6 (PB5)
PB6: J3.1 (MISO), J15.7, U15.7 (PB6)
PB7: J3.3 (SCK), J15.8, U15.8 (PB7)
PC0: J5.1, U15.22 (PC0)
PC1: J5.2, U15.23 (PC1)
PC2: U15.24 (PC2), U20.14 (SER)
PC3: U15.25 (PC3), U20.12 (RCLK), U21.12 (RCLK)
PC4: U15.26 (PC4), U20.11 (SRCLK), U21.11 (SRCLK)
PC5: R33.1, U15.27 (PC5)
PC6: U1.2 (1A), U15.28 (PC6)
PC7: U1.7 (2A), U15.29 (PC7)
PD0: J2.3, U15.14 (PD0)
PD1: R1.1, U15.15 (PD1)
PD2: J14.3, U15.16 (PD2)
PD3: J14.4, U15.17 (PD3)
PD4: J14.5, U15.18 (PD4)
PD5: U15.19 (PD5), U22.1, U22.4, U23.1, U23.4, U23.8, U23.11
PD6: J14.6, U15.20 (PD6)
PD7: J15.1, U15.21 (PD7)
VCC: C18.2, J2.5, J5.3, J9.1, J9.2, J9.3, J9.4, JP7.2 (B), R45.1, U1.16 (VCC1), U11.OUT+, U15.10 (VCC), U20.10 (~SRCLR), U20.16 (VCC), U21.10 (~SRCLR), U21.16 (VCC), U22.14 (V_{DD}), U23.14 (V_{DD})
reset: C13.1, J3.5 (~RST), R45.2, SW9.2, U15.9 (~RESET)

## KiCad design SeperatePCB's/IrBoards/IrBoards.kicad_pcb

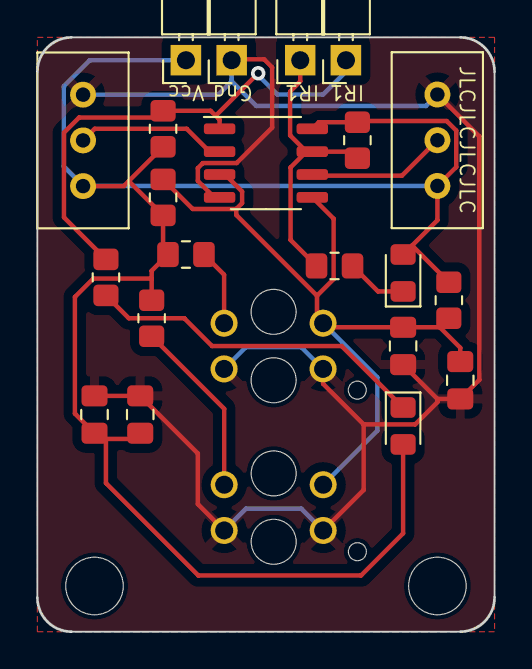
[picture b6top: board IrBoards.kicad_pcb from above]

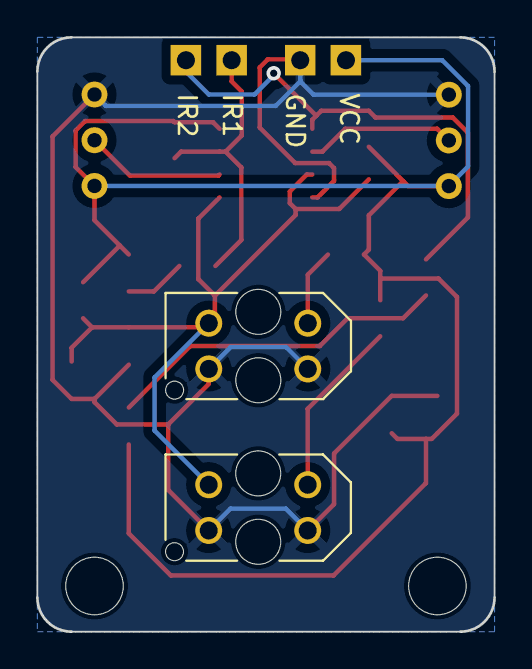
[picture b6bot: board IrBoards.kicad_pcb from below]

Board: 2 copper layers, 25.4 x 33.0 mm, 25 parts (2 on the bottom side), 11 nets.

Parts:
C1, C2, C3, C4: 0.1uF; C_0805_2012Metric_Pad1.18x1.45mm_HandSolder
D1, D2: LED; LED_0805_2012Metric_Pad1.15x1.40mm_HandSolder
H1, H2: MountingHole; MountingHole_3.2mm_M3
J2, J4, J5, J6: Conn_01x01_Pin; PinHeader_1x01_P2.54mm_Horizontal
R1, R5: 180; R_0805_2012Metric_Pad1.20x1.40mm_HandSolder
R2, R3, R6, R7: 10k; R_0805_2012Metric_Pad1.20x1.40mm_HandSolder
R4, R8: 1k; R_0805_2012Metric_Pad1.20x1.40mm_HandSolder
RV1, RV2: 10k; Potentiometer_Bourns_3296W_Vertical
U1: LM393; SO-8_3.9x4.9mm_P1.27mm
U2, U4: TCRT5000; OPTO_TCRT5000

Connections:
/irA0: C2.1, C4.1, R2.2, R6.2, U1.3 (+), U1.5 (+), U2.COLL, U4.COLL
GND: C1.2, C2.2, C3.2, C4.2, J4.1, RV1.3, RV2.3, U1.4 (V-), U2.CATH, U2.E, U4.CATH, U4.E
unnamed: D1.1 (K), R4.1
unnamed: D2.1 (K), R8.1
unnamed: J5.1, R3.2, R4.2, U1.1
unnamed: J6.1, R7.2, R8.2, U1.7
unnamed: R1.2, U2.A
unnamed: R5.2, U4.A
unnamed: RV1.2, U1.2 (-)
unnamed: RV2.2, U1.6 (-)
VCC: C1.1, C3.1, D1.2 (A), D2.2 (A), J2.1, R1.1, R2.1, R3.1, R5.1, R6.1, R7.1, RV1.1, RV2.1, U1.8 (V+)

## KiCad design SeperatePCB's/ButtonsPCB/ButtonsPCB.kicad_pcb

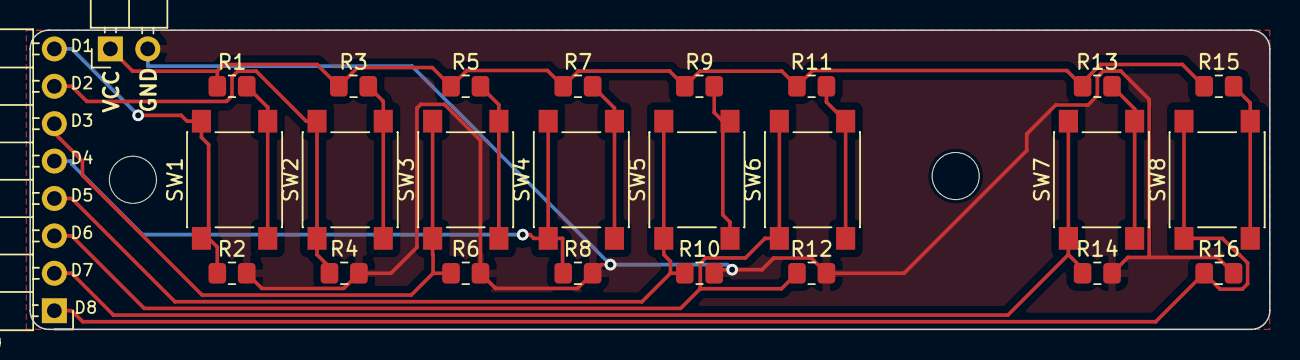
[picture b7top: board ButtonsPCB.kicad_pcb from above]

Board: 2 copper layers, 84.2 x 20.3 mm, 28 parts (0 on the bottom side), 18 nets.

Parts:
H1, H2: MountingHole; MountingHole_3.2mm_M3
J1: Conn_01x02_Pin; PinHeader_1x02_P2.54mm_Horizontal
J9: Conn_01x08_Pin; PinHeader_1x08_P2.54mm_Horizontal
R1, R3, R5, R7, R9, R11, R13, R15: 470Ω; R_0805_2012Metric_Pad1.20x1.40mm_HandSolder
R2, R4, R6, R8, R10, R12, R14, R16: 10KΩ; R_0805_2012Metric_Pad1.20x1.40mm_HandSolder
SW1, SW2, SW3, SW4, SW5, SW6, SW7, SW8: SW_Push; SW_SPST_PTS645

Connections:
GND: J1.2, R2.2, R4.2, R6.2, R8.2, R10.2, R12.2, R14.2, R16.2
unnamed: J9.1, R16.1, SW8.1
unnamed: J9.2, R14.1, SW7.1
unnamed: J9.3, R12.1, SW6.1
unnamed: J9.4, R10.1, SW5.1
unnamed: J9.5, R8.1, SW4.1
unnamed: J9.6, R6.1, SW3.1
unnamed: J9.7, R4.1, SW2.1
unnamed: J9.8, R2.1, SW1.1
unnamed: R1.2, SW1.2
unnamed: R3.2, SW2.2
unnamed: R5.2, SW3.2
unnamed: R7.2, SW4.2
unnamed: R9.2, SW5.2
unnamed: R11.2, SW6.2
unnamed: R13.2, SW7.2
unnamed: R15.2, SW8.2
VCC: J1.1, R1.1, R3.1, R5.1, R7.1, R9.1, R11.1, R13.1, R15.1

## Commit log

2024-06-03 initial
2024-06-03 programma
2024-06-03 beschrijving
